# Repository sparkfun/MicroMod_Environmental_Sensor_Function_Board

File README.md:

SparkFun MicroMod Environmental Sensor Function Board
========================================

[*SparkFun MicroMod Environmental Sensor Function Board (SEN-18632)*](https://www.sparkfun.com/products/18632)

The SparkFun MicroMod Environmental Function Board adds additional sensing options to the MicroMod Processor Boards. This Function Board includes three sensors to monitor air quality (SGP40), humidity & temperature (SHTC3), and CO<sub>2</sub> concentrations (STC31) in your indoor environment. To make it even easier to use, all communication is over the MicroMod's I<sup>2</sup>C bus!

* The SGP40 measures the quality of the air in your room or house. The SGP40 uses a metal oxide (MOx) sensor with a temperature controlled micro hotplate and provides a humidity-compensated volatile organic compound (VOC) based indoor air quality signal. Both the sensing element and VOC Algorithm feature an unmatched robustness against contaminating gases present in real world applications enabling a unique long term stability as well as low drift and device to device variation.

* The SHTC3 is a highly accurate digital humidity and temperature sensor. The SHTC3 uses a capacitive humidity sensor with a relative humidity measurement range of 0 to 100% RH and bandgap temperature sensor with a temperature measurement range of -40&deg;C to 125&deg;C. The SHTC3 builds on the success of their SHTC1 sensor with higher accuracy (±2% RH, ±0.2&deg;C) than its predecessor, enabling greater flexibility.

* The STC31 measures CO<sub>2</sub> concentrations based on thermal conductivity and has two CO<sub>2</sub> measurement ranges: 0 to 25 vol%; and 0 to 100 vol%. The measurement repeatability is 0.2 vol%, with a stability of 0.025 vol% / °C. The measurement accuracy depends on the measurement range: 0.5 vol% + 3% measured value; 1 vol% + 3% measured value. Using measurements from the SHTC3, the STC31 is able to provide humidity-compensated measurements together with improved temperature compensation.  The STC31 can compensate for atmospheric pressure too - which is handy if, like us, you’re up in the mountains!

The outstanding performance of these three sensors is based on Sensirion’s patented CMOSens<sup>&reg;</sup> technology, which combines the sensor element, signal processing, and digital calibration on a small CMOS chip. The well-proven CMOS technology is perfectly suited for high-quality mass production and is the ideal choice for demanding and cost-sensitive OEM applications.

Utilizing our handy M.2 MicroMod connector, no soldering is required to connect it to your system. Simply match up the key on your processor and function board's beveled edge connector to their respective key on the M.2 connector, then secure them to the main board with screws. The MicroMod Environmental Function Board can then be read via the I<sup>2</sup>C port. The board is equipped with the AP2112 3.3V voltage regulator, I<sup>2</sup>C pull-up resistors, power LED, jumper to disable the LED, and jumpers for alternative STC31 addresses. 

Repository Contents
-------------------

* **/Firmware** - Arduino example code from the tutorial
* **/Hardware** - Eagle design files (.brd, .sch)
* **/Production** - Production panel files (.brd)

Documentation
--------------

* **[Installing an Arduino Library Guide](https://learn.sparkfun.com/tutorials/installing-an-arduino-library/all)** - Basic information on how to install an Arduino library.
* **Arduino Libraries**
  * **[SGP40](https://github.com/sparkfun/SparkFun_SGP40_Arduino_Library)**
  * **[SHTC3](https://github.com/sparkfun/SparkFun_SHTC3_Arduino_Library)**
  * **[STC3X](https://github.com/sparkfun/SparkFun_STC3x_Arduino_Library)**
* **[Hookup Guide](https://learn.sparkfun.com/tutorials/2001)** - Basic hookup guide

Product Versions
----------------

* [SEN-18632](https://www.sparkfun.com/products/18632)- Initial release

Version History
---------------

* v1.0 - Initial Release

License Information
-------------------

This product is _**open source**_! 

Please review the LICENSE.md file for license information. 

If you have any questions or concerns on licensing, please contact technical support on our [SparkFun forums](https://forum.sparkfun.com/viewforum.php?f=152).

Distributed as-is; no warranty is given.

- Your friends at SparkFun.

_<COLLABORATION CREDIT>_

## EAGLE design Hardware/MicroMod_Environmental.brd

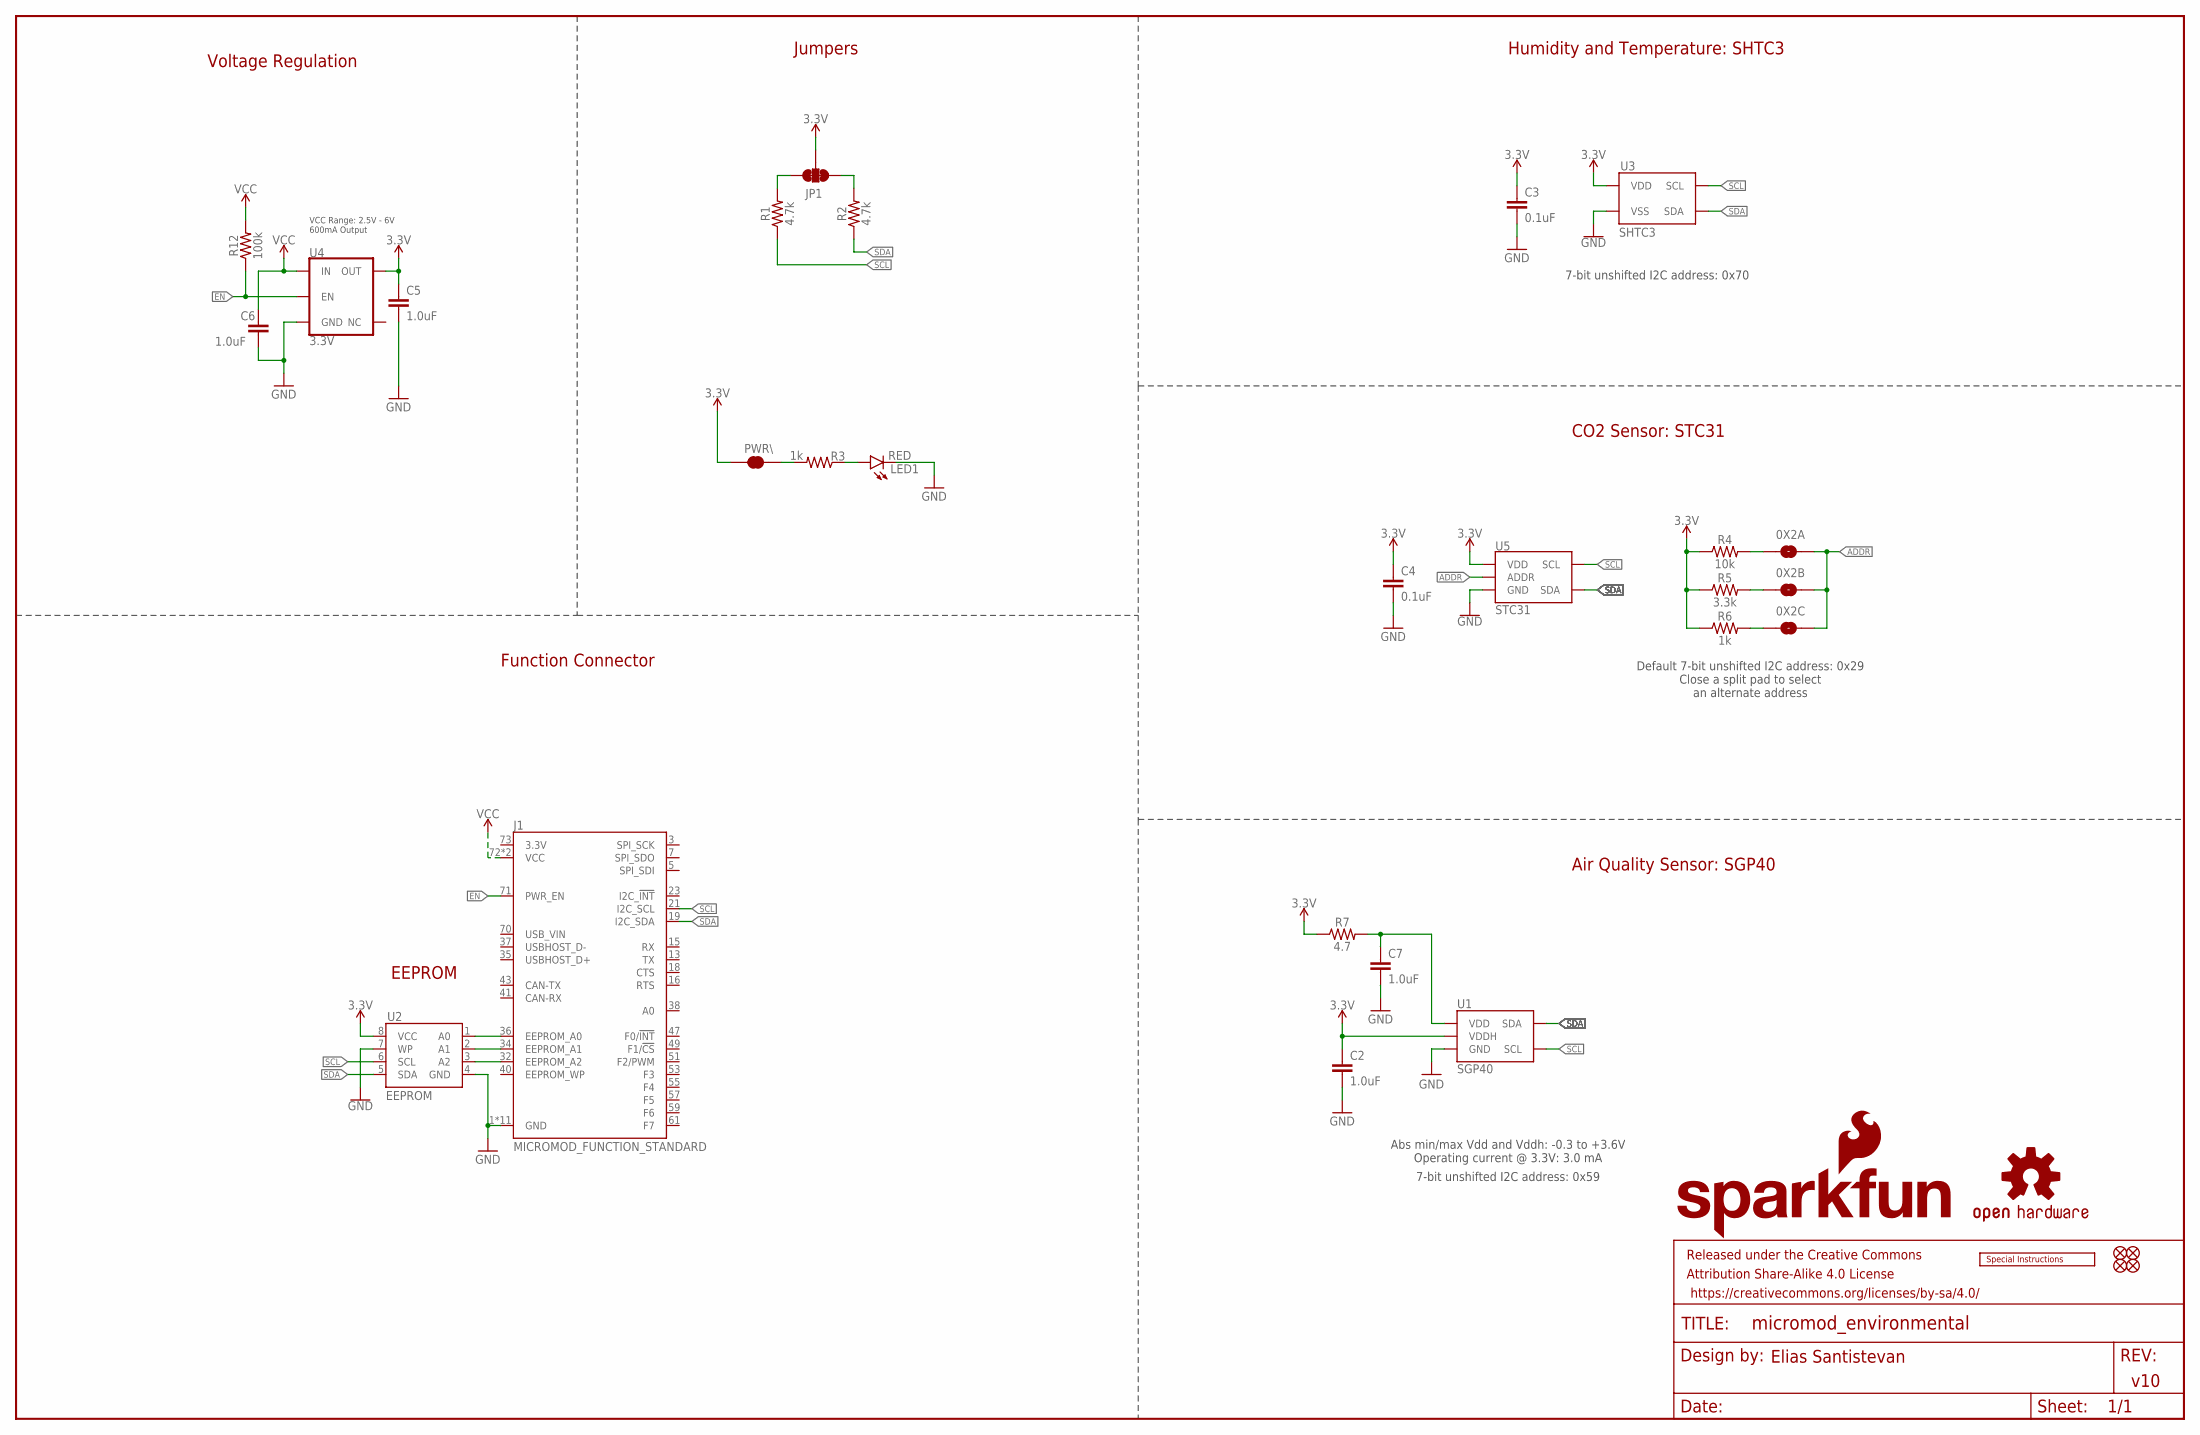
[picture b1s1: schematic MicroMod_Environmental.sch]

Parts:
0X2A, 0X2B, 0X2C: JUMPER-SMT_2_NO_SILK; SMT-JUMPER_2_NO_SILK
C2, C5, C6, C7: 1.0uF; 0603
C3, C4: 0.1uF; 0603
FD1, FD2, FD3, FD4: FIDUCIAL1X2; FIDUCIAL-1X2
FRAME1: FRAME-LEDGER; CREATIVE_COMMONS
J1: MICROMOD_FUNCTION_STANDARD; M.2-CARD-E-22_FUNCTION_STANDARD
JP1: JUMPER-SMT_3_2-NC_TRACE_SILK; SMT-JUMPER_3_2-NC_TRACE_SILK
LED1: RED; LED-0603
LOGO1: SFE_LOGO_NAME_FLAME.2_INCH; SFE_LOGO_NAME_FLAME_.2
LOGO2: OSHW-LOGOS; OSHW-LOGO-S
LOGO3: SPECIAL_INSTRUCTIONS-ORDERING; ORDERING_INSTRUCTIONS
PWR\: JUMPER-SMT_2_NC_TRACE_SILK; SMT-JUMPER_2_NC_TRACE_SILK
R1, R2: 4.7k; 0603
R3, R6: 1k; 0603
R4: 10k; 0603
R5: 3.3k; 0603
R7: 4.7; 0603
R12: 100k; 0603
U1: SGP40
U2: EEPROM; SO08
U3: SHTC3
U4: 3.3V; SOT23-5
U5: STC31

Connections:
3.3V: C2.1, C3.1, C4.1, C5.1, JP1.2, PWR\.2, R4.1, R5.1, R6.1, R7.1, U1.5 (VDDH), U2.8 (VCC), U3.1 (VDD), U4.5 (OUT), U5.6 (VDD)
A0: J1.36 (EEPROM_A0), U2.1 (A0)
A1: J1.34 (EEPROM_A1), U2.2 (A1)
A2: J1.32 (EEPROM_A2), U2.3 (A2)
ADDR: 0X2A.2, 0X2B.2, 0X2C.2, U5.3 (ADDR)
EN: J1.71 (PWR_EN), R12.1, U4.3 (EN)
GND: C2.2, C3.2, C4.2, C5.2, C6.2, C7.2, J1.1 (GND), J1.33 (GND), J1.39 (GND), J1.45 (GND), J1.75 (GND), J1.GND1 (GND), J1.GND2 (GND), J1.GND3 (GND), J1.GND4 (GND), J1.GND5 (GND), J1.GND6 (GND), LED1.C, U1.2 (GND), U1.4 (GND), U1.DIEPAD (GND), U2.4 (GND), U2.7 (WP), U3.4 (VSS), U3.5 (VSS), U4.2 (GND), U5.1 (GND), U5.5 (GND), U5.9 (GND), U5.11 (GND), U5.DIEPAD (GND)
unnamed: PWR\.1, R3.2
unnamed: C7.1, R7.2, U1.1 (VDD)
unnamed: JP1.3, R1.2
unnamed: JP1.1, R2.2
unnamed: 0X2A.1, R4.2
unnamed: 0X2B.1, R5.2
unnamed: 0X2C.1, R6.2
unnamed: LED1.A, R3.1
SCL: J1.21 (I2C_SCL), R1.1, U1.6 (SCL), U2.6 (SCL), U3.2 (SCL), U5.4 (SCL)
SDA: J1.19 (I2C_SDA), R2.1, U1.3 (SDA), U2.5 (SDA), U3.3 (SDA), U5.7 (SDA)
VCC: C6.1, J1.72 (VCC), J1.74 (VCC), R12.2, U4.1 (IN)

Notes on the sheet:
Elias Santistevan
v10
VCC Range: 2.5V - 6V 600mA Output
Default 7-bit unshifted I2C address: 0x29 Close a split pad to select an alternate address
7-bit unshifted I2C address: 0x70
7-bit unshifted I2C address: 0x59
Abs min/max Vdd and Vddh: -0.3 to +3.6V Operating current @ 3.3V: 3.0 mA
EEPROM
Voltage Regulation
Jumpers
Humidity and Temperature: SHTC3
CO2 Sensor: STC31
Function Connector
Air Quality Sensor: SGP40

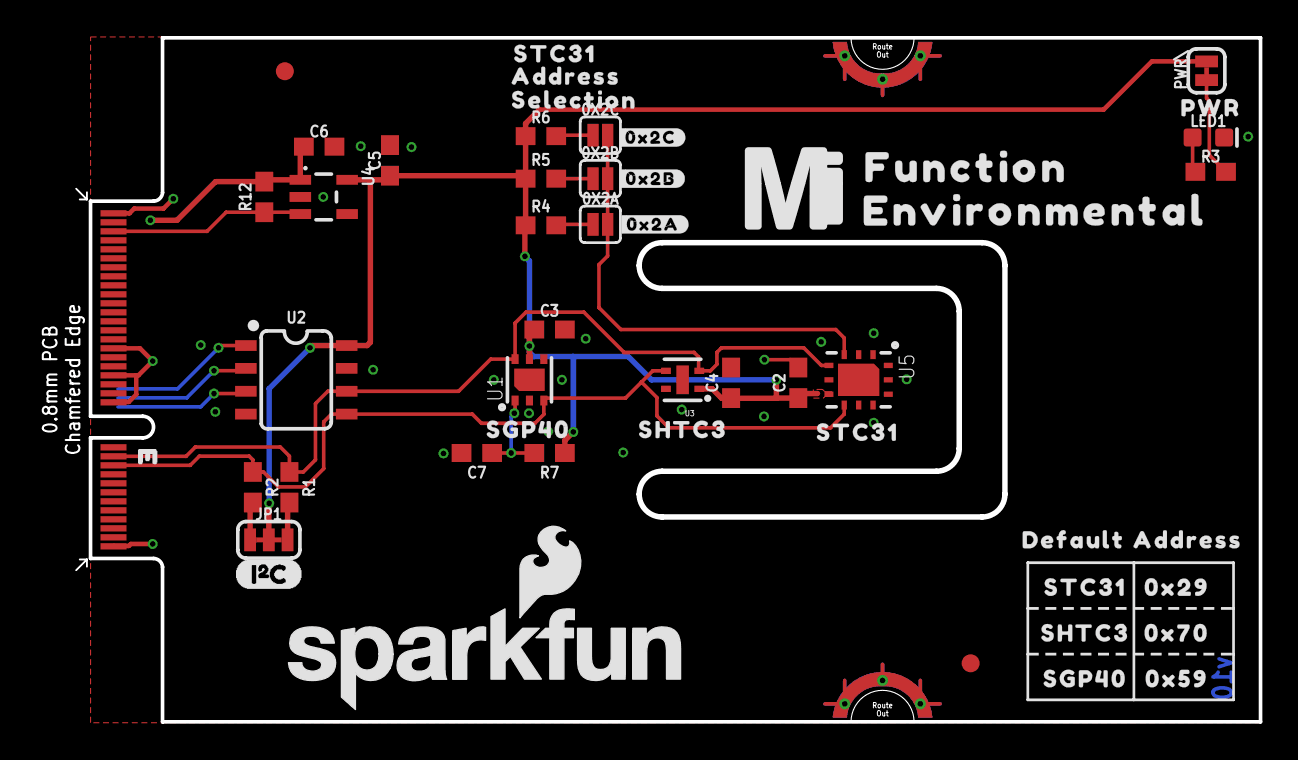
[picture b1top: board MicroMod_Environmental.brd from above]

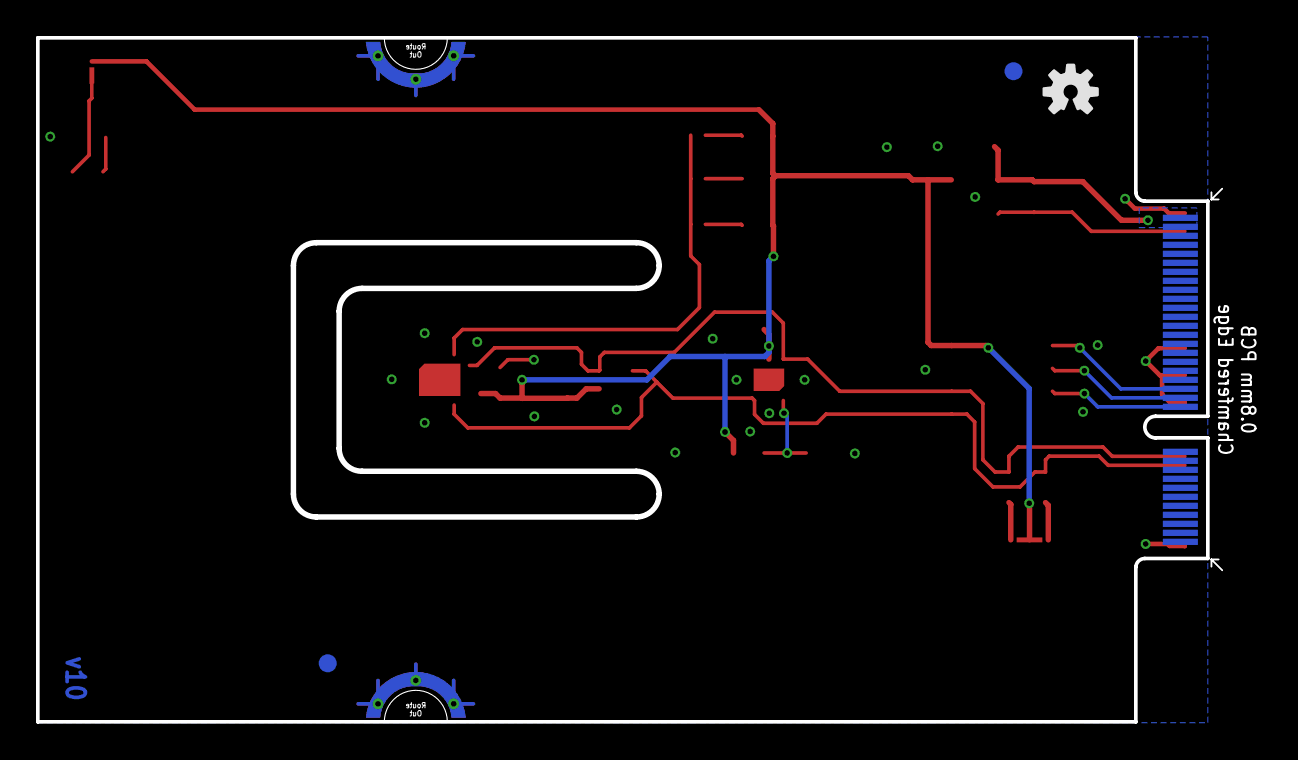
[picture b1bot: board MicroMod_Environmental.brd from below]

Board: 2 copper layers, 67.8 x 37.9 mm, 56 parts (3 on the bottom side), 18 nets.

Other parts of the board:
U$1: #0X2A#21
U$2: #0X2B#21
U$3: #0X2C#21
U$4: PWR321541
U$5: FUNCTION524
U$6: ENVIRONMENTAL526
U$7: MICROMOD_MI_LOGO_1
U$8: I2C
U$9, U$15: ADDRESS40313505
U$10: 0X2940313520
U$11, U$18: SGP40313503
U$12, U$17: SHTC3501
U$13, U$16, U$22: STC313502
U$14: DEFAULT40313504
U$19: 0X5940313520
U$20: 0X7040313520
U$21: SELECTION40313506

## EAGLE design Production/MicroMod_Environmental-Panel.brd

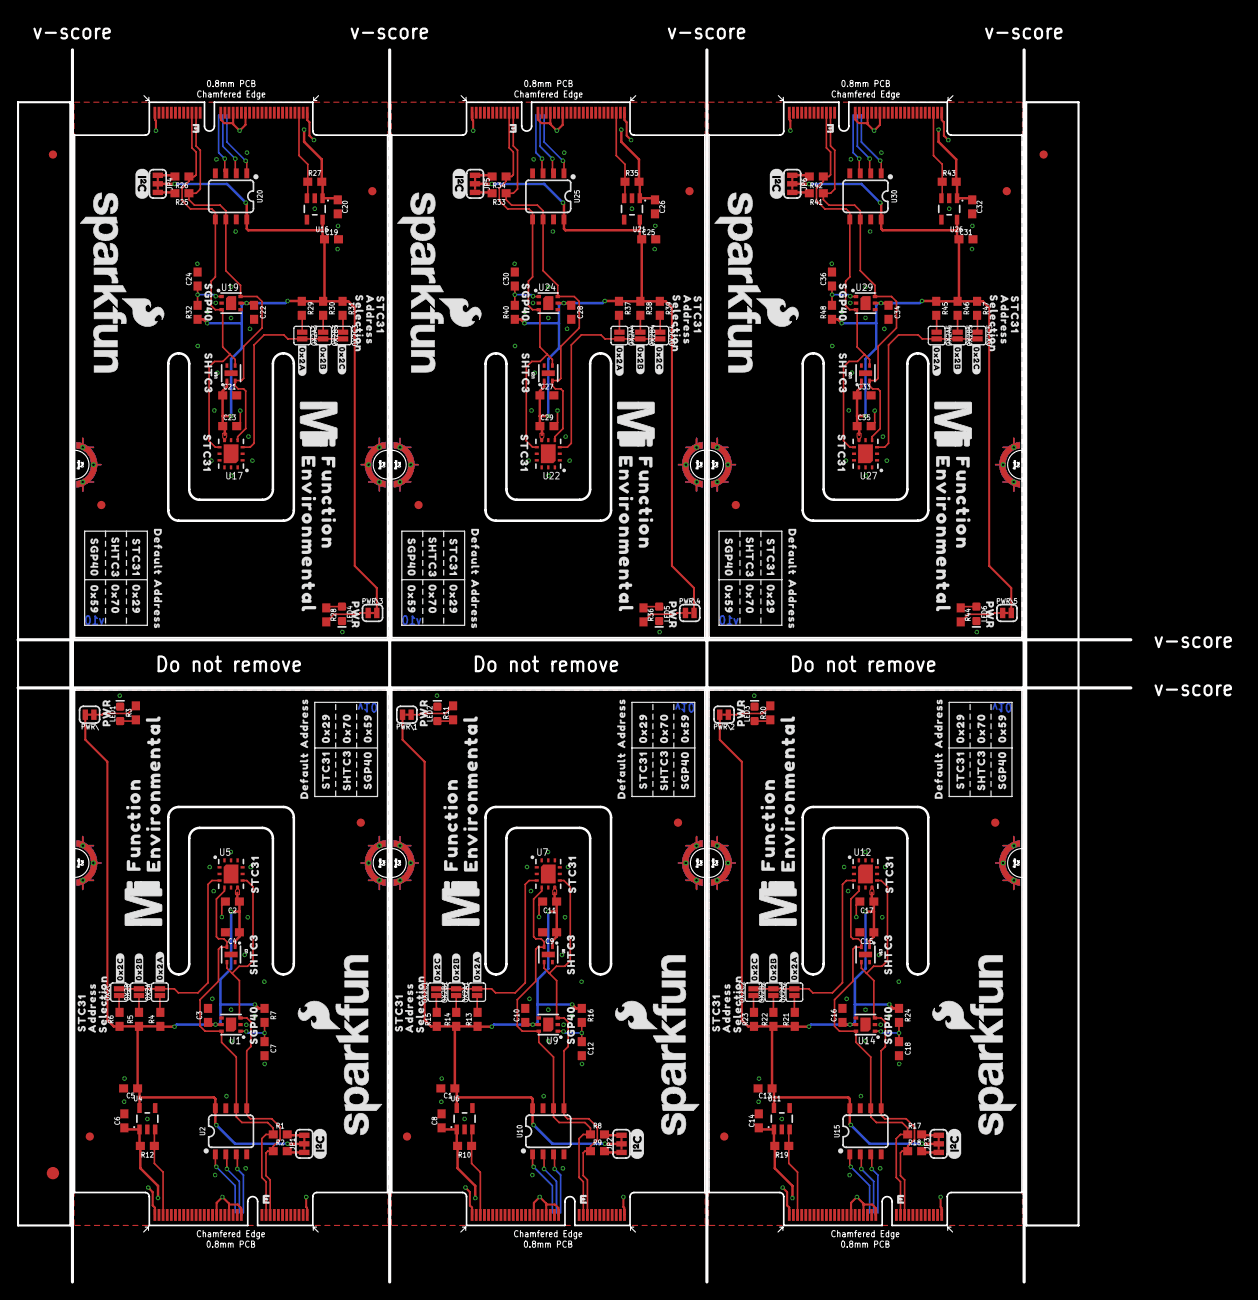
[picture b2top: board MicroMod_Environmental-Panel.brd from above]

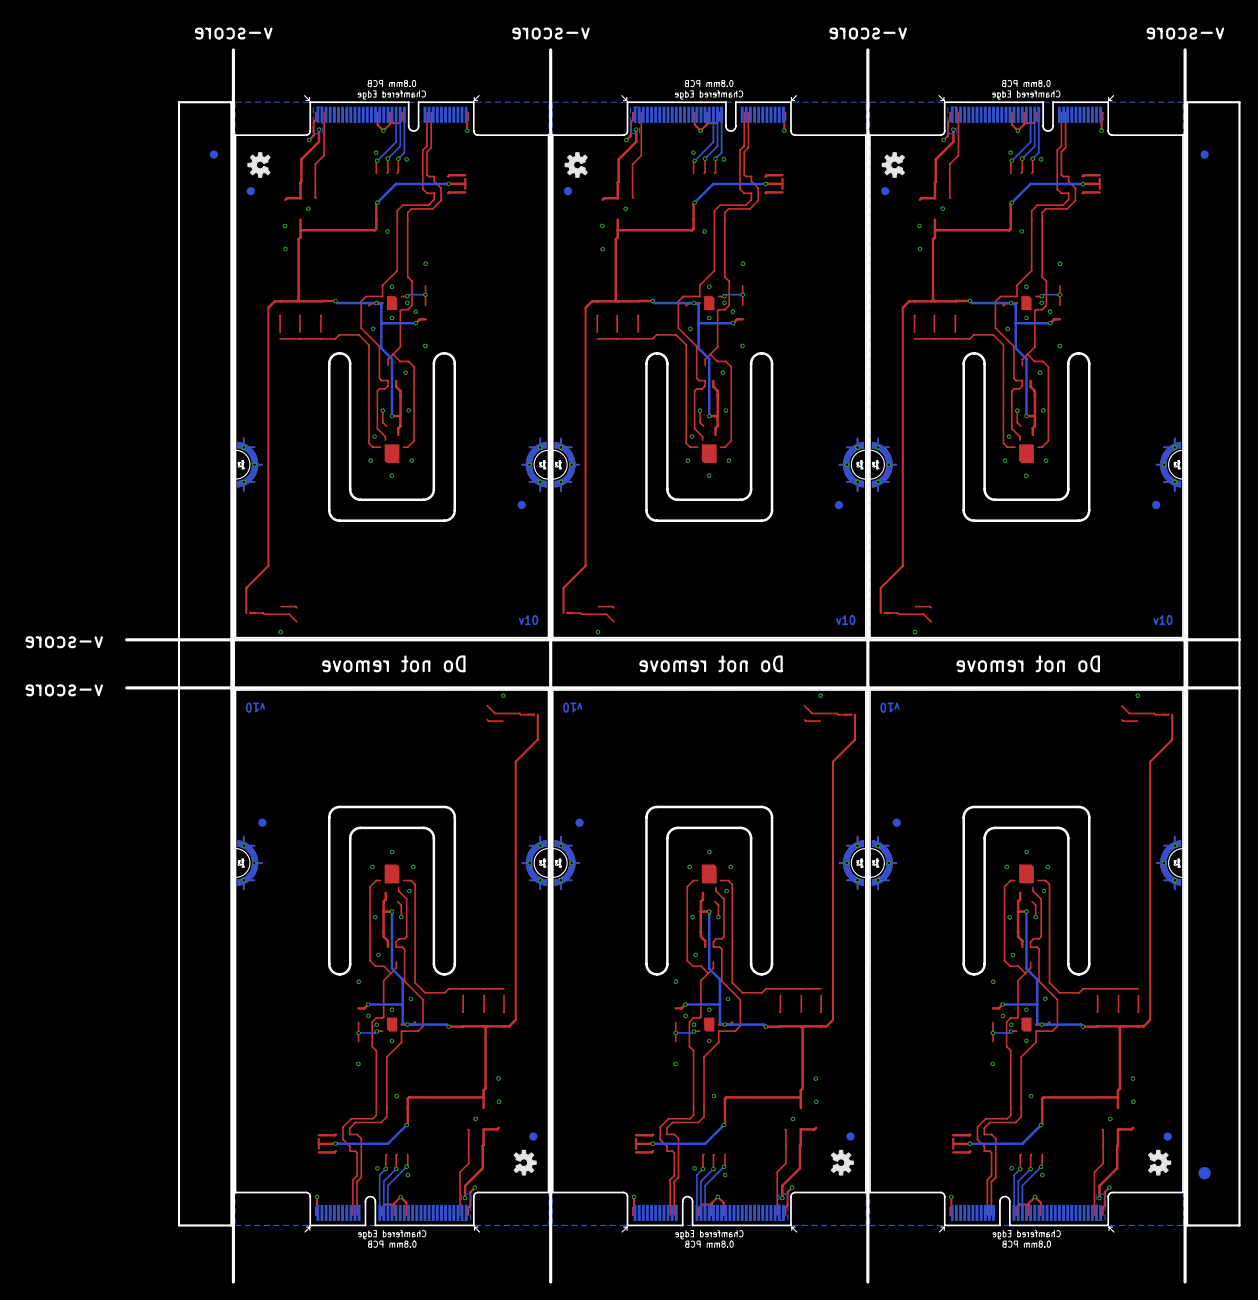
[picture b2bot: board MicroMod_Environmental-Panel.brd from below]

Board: 2 copper layers, 148.3 x 153.4 mm, 330 parts (21 on the bottom side), 108 nets.

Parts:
0X2A, 0X2A1, 0X2A2, 0X2A3, 0X2A4, 0X2A5, 0X2B, 0X2B1, 0X2B2, 0X2B3, 0X2B4, 0X2B5, 0X2C, 0X2C1, 0X2C2, 0X2C3, 0X2C4, 0X2C5: JUMPER-SMT_2_NO_SILK; SMT-JUMPER_2_NO_SILK
C1, C2, C5, C6, C7, C8, C11, C12, C13, C14, C17, C18, C19, C20, C23, C24, C25, C26, C29, C30, C31, C32, C35, C36: 1.0uF; 0603
C3, C4, C9, C10, C15, C16, C21, C22, C27, C28, C33, C34: 0.1uF; 0603
E$1, E$2, E$3, E$4: FIDUCIAL-1X2
E$5, E$6: FIDUCIAL-1.5X3
FD1, FD2, FD3, FD4, FD5, FD6, FD7, FD8, FD9, FD10, FD11, FD12, FD13, FD14, FD15, FD16, FD17, FD18, FD19, FD20, FD21, FD22, FD23, FD24: FIDUCIAL1X2; FIDUCIAL-1X2
J1, J2, J3, J4, J5, J6: MICROMOD_STANDARD; M.2-CARD-E-22_FUNCTION_STANDARD
JP1, JP2, JP3, JP4, JP5, JP6: JUMPER-SMT_3_2-NC_TRACE_SILK; SMT-JUMPER_3_2-NC_TRACE_SILK
LED1, LED2, LED3, LED4, LED5, LED6: RED; LED-0603
LOGO1, LOGO3, LOGO5, LOGO7, LOGO9, LOGO11: SFE_LOGO_NAME_FLAME.2_INCH; SFE_LOGO_NAME_FLAME_.2
LOGO2, LOGO4, LOGO6, LOGO8, LOGO10, LOGO12: OSHW-LOGOS; OSHW-LOGO-S
PWR\, PWR\1, PWR\2, PWR\3, PWR\4, PWR\5: JUMPER-SMT_2_NC_TRACE_SILK; SMT-JUMPER_2_NC_TRACE_SILK
R1, R2, R8, R9, R17, R18, R25, R26, R33, R34, R41, R42: 4.7k; 0603
R3, R6, R11, R15, R20, R23, R28, R31, R36, R39, R44, R47: 1k; 0603
R4, R13, R21, R29, R37, R45: 10k; 0603
R5, R14, R22, R30, R38, R46: 3.3k; 0603
R7, R16, R24, R32, R40, R48: 4.7; 0603
R10, R12, R19, R27, R35, R43: 100k; 0603
U1, U9, U14, U19, U24, U29: SGP40
U2, U10, U15, U20, U25, U30: EEPROM; SO08
U3, U8, U13, U18, U23, U28: SHTC3
U4, U6, U11, U16, U21, U26: 3.3V; SOT23-5
U5, U7, U12, U17, U22, U27: STC31
U$1, U$23, U$45, U$67, U$89, U$111: #0X2A#21
U$2, U$24, U$46, U$68, U$90, U$112: #0X2B#21
U$3, U$25, U$47, U$69, U$91, U$113: #0X2C#21
U$4, U$26, U$48, U$70, U$92, U$114: PWR321541
U$5, U$27, U$49, U$71, U$93, U$115: FUNCTION524
U$6, U$28, U$50, U$72, U$94, U$116: ENVIRONMENTAL526
U$7, U$29, U$51, U$73, U$95, U$117: MICROMOD_MI_LOGO_1
U$8, U$30, U$52, U$74, U$96, U$118: I2C
U$9, U$15, U$35, U$42, U$57, U$64, U$79, U$86, U$101, U$108, U$123, U$130: ADDRESS40313505
U$10, U$39, U$61, U$83, U$105, U$127: 0X2940313520
U$11, U$18, U$31, U$38, U$53, U$60, U$75, U$82, U$97, U$104, U$119, U$126: SGP40313503
U$12, U$17, U$32, U$37, U$54, U$59, U$76, U$81, U$98, U$103, U$120, U$125: SHTC3501
U$13, U$16, U$22, U$33, U$36, U$44, U$55, U$58, U$66, U$77, U$80, U$88, U$99, U$102, U$110, U$121, U$124, U$132: STC313502
U$14, U$34, U$56, U$78, U$100, U$122: DEFAULT40313504
U$19, U$40, U$62, U$84, U$106, U$128: 0X5940313520
U$20, U$41, U$63, U$85, U$107, U$129: 0X7040313520
U$21, U$43, U$65, U$87, U$109, U$131: SELECTION40313506

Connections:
3.3V: C2.1, C3.1, C4.1, C5.1, JP1.2, PWR\.2, R4.1, R5.1, R6.1, R7.1, U1.5, U2.8, U3.1, U4.5, U5.6
3.3V1: C1.1, C9.1, C10.1, C11.1, JP2.2, PWR\1.2, R13.1, R14.1, R15.1, R16.1, U6.5, U7.6, U8.1, U9.5, U10.8
3.3V2: C13.1, C15.1, C16.1, C17.1, JP3.2, PWR\2.2, R21.1, R22.1, R23.1, R24.1, U11.5, U12.6, U13.1, U14.5, U15.8
3.3V3: C19.1, C21.1, C22.1, C23.1, JP4.2, PWR\3.2, R29.1, R30.1, R31.1, R32.1, U16.5, U17.6, U18.1, U19.5, U20.8
3.3V4: C25.1, C27.1, C28.1, C29.1, JP5.2, PWR\4.2, R37.1, R38.1, R39.1, R40.1, U21.5, U22.6, U23.1, U24.5, U25.8
3.3V5: C31.1, C33.1, C34.1, C35.1, JP6.2, PWR\5.2, R45.1, R46.1, R47.1, R48.1, U26.5, U27.6, U28.1, U29.5, U30.8
A0: J1.36, U2.1
A1: J1.34, U2.2
A2: J1.32, U2.3
A3: J2.36, U10.1
A4: J2.32, U10.3
A5: J2.34, U10.2
A6: J3.36, U15.1
A7: J3.32, U15.3
A8: J3.34, U15.2
A9: J4.36, U20.1
A10: J4.32, U20.3
A11: J4.34, U20.2
A12: J5.36, U25.1
A13: J5.32, U25.3
A14: J5.34, U25.2
A15: J6.36, U30.1
A16: J6.32, U30.3
A17: J6.34, U30.2
ADDR: 0X2A.2, 0X2B.2, 0X2C.2, U5.3
ADDR1: 0X2A1.2, 0X2B1.2, 0X2C1.2, U7.3
ADDR2: 0X2A2.2, 0X2B2.2, 0X2C2.2, U12.3
ADDR3: 0X2A3.2, 0X2B3.2, 0X2C3.2, U17.3
ADDR4: 0X2A4.2, 0X2B4.2, 0X2C4.2, U22.3
ADDR5: 0X2A5.2, 0X2B5.2, 0X2C5.2, U27.3
EN: J1.71, R12.1, U4.3
EN1: J2.71, R10.1, U6.3
EN2: J3.71, R19.1, U11.3
EN3: J4.71, R27.1, U16.3
EN4: J5.71, R35.1, U21.3
EN5: J6.71, R43.1, U26.3
GND: C2.2, C3.2, C4.2, C5.2, C6.2, C7.2, J1.1, J1.33, J1.39, J1.45, J1.75, J1.GND1, J1.GND2, J1.GND3, J1.GND4, J1.GND5, J1.GND6, LED1.C, U1.2, U1.4, U1.DIEPAD, U2.4, U2.7, U3.4, U3.5, U4.2, U5.1, U5.5, U5.9, U5.11, U5.DIEPAD
GND1: C1.2, C8.2, C9.2, C10.2, C11.2, C12.2, J2.1, J2.33, J2.39, J2.45, J2.75, J2.GND1, J2.GND2, J2.GND3, J2.GND4, J2.GND5, J2.GND6, LED2.C, U6.2, U7.1, U7.5, U7.9, U7.11, U7.DIEPAD, U8.4, U8.5, U9.2, U9.4, U9.DIEPAD, U10.4, U10.7
GND2: C13.2, C14.2, C15.2, C16.2, C17.2, C18.2, J3.1, J3.33, J3.39, J3.45, J3.75, J3.GND1, J3.GND2, J3.GND3, J3.GND4, J3.GND5, J3.GND6, LED3.C, U11.2, U12.1, U12.5, U12.9, U12.11, U12.DIEPAD, U13.4, U13.5, U14.2, U14.4, U14.DIEPAD, U15.4, U15.7
GND3: C19.2, C20.2, C21.2, C22.2, C23.2, C24.2, J4.1, J4.33, J4.39, J4.45, J4.75, J4.GND1, J4.GND2, J4.GND3, J4.GND4, J4.GND5, J4.GND6, LED4.C, U16.2, U17.1, U17.5, U17.9, U17.11, U17.DIEPAD, U18.4, U18.5, U19.2, U19.4, U19.DIEPAD, U20.4, U20.7
GND4: C25.2, C26.2, C27.2, C28.2, C29.2, C30.2, J5.1, J5.33, J5.39, J5.45, J5.75, J5.GND1, J5.GND2, J5.GND3, J5.GND4, J5.GND5, J5.GND6, LED5.C, U21.2, U22.1, U22.5, U22.9, U22.11, U22.DIEPAD, U23.4, U23.5, U24.2, U24.4, U24.DIEPAD, U25.4, U25.7
GND5: C31.2, C32.2, C33.2, C34.2, C35.2, C36.2, J6.1, J6.33, J6.39, J6.45, J6.75, J6.GND1, J6.GND2, J6.GND3, J6.GND4, J6.GND5, J6.GND6, LED6.C, U26.2, U27.1, U27.5, U27.9, U27.11, U27.DIEPAD, U28.4, U28.5, U29.2, U29.4, U29.DIEPAD, U30.4, U30.7
unnamed: PWR\.1, R3.2
unnamed: C7.1, R7.2, U1.1
unnamed: JP1.3, R1.2
unnamed: JP1.1, R2.2
unnamed: 0X2A.1, R4.2
unnamed: 0X2B.1, R5.2
unnamed: 0X2C.1, R6.2
unnamed: LED2.A, R11.1
unnamed: PWR\1.1, R11.2
unnamed: LED1.A, R3.1
unnamed: 0X2A1.1, R13.2
unnamed: 0X2B1.1, R14.2
unnamed: 0X2C1.1, R15.2
unnamed: C12.1, R16.2, U9.1
unnamed: JP2.3, R8.2
unnamed: JP2.1, R9.2
unnamed: LED3.A, R20.1
unnamed: PWR\2.1, R20.2
unnamed: 0X2A2.1, R21.2
unnamed: 0X2B2.1, R22.2
unnamed: 0X2C2.1, R23.2
unnamed: C18.1, R24.2, U14.1
unnamed: JP3.3, R17.2
unnamed: JP3.1, R18.2
unnamed: LED4.A, R28.1
unnamed: PWR\3.1, R28.2
unnamed: 0X2A3.1, R29.2
unnamed: 0X2B3.1, R30.2
unnamed: 0X2C3.1, R31.2
unnamed: C24.1, R32.2, U19.1
unnamed: JP4.3, R25.2
unnamed: JP4.1, R26.2
unnamed: LED5.A, R36.1
unnamed: PWR\4.1, R36.2
unnamed: 0X2A4.1, R37.2
unnamed: 0X2B4.1, R38.2
unnamed: 0X2C4.1, R39.2
unnamed: C30.1, R40.2, U24.1
unnamed: JP5.3, R33.2
unnamed: JP5.1, R34.2
unnamed: LED6.A, R44.1
unnamed: PWR\5.1, R44.2
unnamed: 0X2A5.1, R45.2
unnamed: 0X2B5.1, R46.2
unnamed: 0X2C5.1, R47.2
unnamed: C36.1, R48.2, U29.1
unnamed: JP6.3, R41.2
unnamed: JP6.1, R42.2
SCL: J1.21, R1.1, U1.6, U2.6, U3.2, U5.4
SCL1: J2.21, R8.1, U7.4, U8.2, U9.6, U10.6
SCL2: J3.21, R17.1, U12.4, U13.2, U14.6, U15.6
SCL3: J4.21, R25.1, U17.4, U18.2, U19.6, U20.6
SCL4: J5.21, R33.1, U22.4, U23.2, U24.6, U25.6
SCL5: J6.21, R41.1, U27.4, U28.2, U29.6, U30.6
SDA: J1.19, R2.1, U1.3, U2.5, U3.3, U5.7
SDA1: J2.19, R9.1, U7.7, U8.3, U9.3, U10.5
SDA2: J3.19, R18.1, U12.7, U13.3, U14.3, U15.5
SDA3: J4.19, R26.1, U17.7, U18.3, U19.3, U20.5
SDA4: J5.19, R34.1, U22.7, U23.3, U24.3, U25.5
SDA5: J6.19, R42.1, U27.7, U28.3, U29.3, U30.5
VCC: C6.1, J1.72, J1.74, R12.2, U4.1
VCC1: C8.1, J2.72, J2.74, R10.2, U6.1
VCC2: C14.1, J3.72, J3.74, R19.2, U11.1
VCC3: C20.1, J4.72, J4.74, R27.2, U16.1
VCC4: C26.1, J5.72, J5.74, R35.2, U21.1
VCC5: C32.1, J6.72, J6.74, R43.2, U26.1

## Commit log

2021-08-27 Routed
2021-08-31 Small tweaks to traces
2021-09-01 Adds silk, fiducials, and version number
    * Adds text to part boxes in schematic
2021-09-07 Reroutes board
2021-09-09 Adds Silk for default I2C address
2021-09-09 Adds some vias, moves some silk
2021-09-10 Adds address table in silk, adds a more symmetrical cutout around IC's, labels ICs in silk
2021-09-10 Fixes air wire
2021-09-10 Panel v10
2021-09-13 Moves production files to correct loaction
2021-09-27 Adds pullup and jumper to the EEPROM's write protect, brings WP pin to card's edge
2021-10-15 Updates pull up resistors to 2.2k from 4.7k
2021-10-15 Updates pullup resistor to 2.2k from 4.7k
2021-11-02 Add combined examples
2021-11-03 Updates Function Board symbol
2021-11-04 Update Description, Comments, Adjust White Space, And Add Pause for SAMD51
2021-11-04 Update Comment
2021-11-04 Disable while loop for Serial
    Disable while loop for SAMD51 and leaving it up to the users to uncomment that have the native USB
2021-11-11 Updates function board symbol to new one in the official SFE eagle library repo

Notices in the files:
parts and their libraries:
SparkFun-Aesthetics: Licensing: Creative Commons ShareAlike 4.0 International - https://creativecommons.org/licenses/by-sa/4.0
SparkFun-Aesthetics: Released under the Creative Commons Attribution Share-Alike 4.0 License
SparkFun-Aesthetics: https://creativecommons.org/licenses/by-sa/4.0
